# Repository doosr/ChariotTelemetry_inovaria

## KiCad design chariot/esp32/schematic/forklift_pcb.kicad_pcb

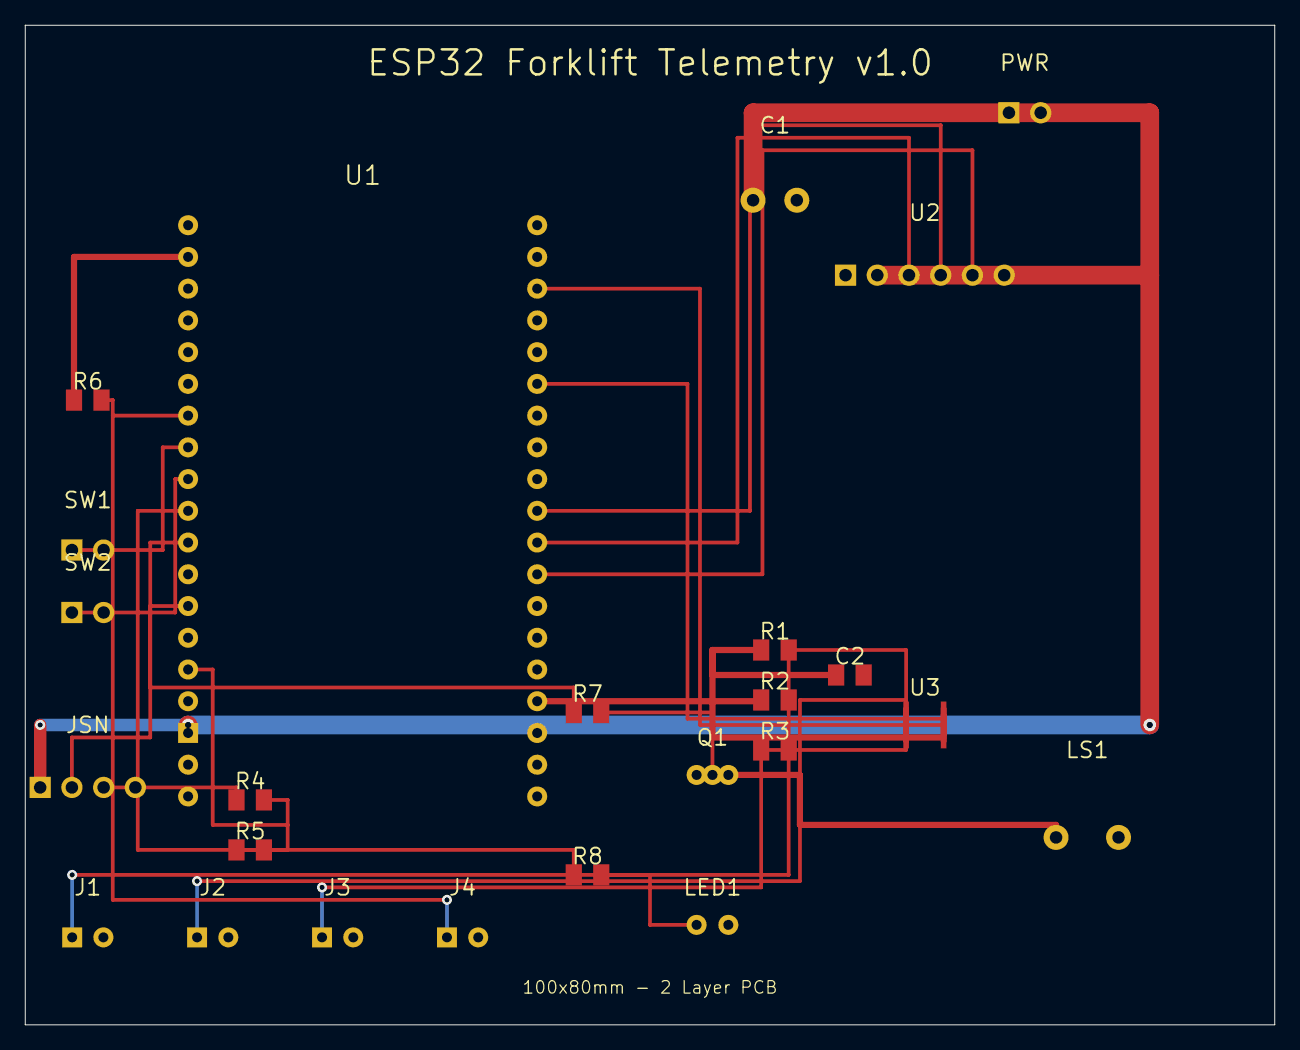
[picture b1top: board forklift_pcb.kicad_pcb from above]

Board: 2 copper layers, 100.0 x 80.0 mm, 24 parts (0 on the bottom side), 20 nets.

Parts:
C1: 100uF 16V; CP_Radial_D8.0mm_P3.50mm
C2: 100nF; C_0805_2012Metric
J1: SENS_OIL; JST_XH_B2B-XH-A_1x02_P2.50mm_Vertical
J2: SENS_FUEL; JST_XH_B2B-XH-A_1x02_P2.50mm_Vertical
J3: SENS_NTC; JST_XH_B2B-XH-A_1x02_P2.50mm_Vertical
J4: SENS_RPM; JST_XH_B2B-XH-A_1x02_P2.50mm_Vertical
JSN: JSN-SR04T; PinHeader_1x04_P2.54mm_Vertical
LED1: LED Green; LED_D3.0mm
LS1: Buzzer 5V; Buzzer_12x9.5mm
PWR: +5V INPUT; PinHeader_1x02_P2.54mm_Vertical
Q1: 2N2222; TO-92_Inline
R1, R2, R3, R5, R7: 1k; R_0805_2012Metric
R4: 2k; R_0805_2012Metric
R6: 10k; R_0805_2012Metric
R8: 330R; R_0805_2012Metric
SW1: FWD Switch; PinHeader_1x02_P2.54mm_Vertical
SW2: REV Switch; PinHeader_1x02_P2.54mm_Vertical
U1: ESP32-DevKitC-32D
U2: SIM808 Module; PinHeader_1x06_P2.54mm_Vertical
U3: ADS1115; MSOP-10_3x3mm_P0.5mm

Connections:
ALARM_5V: LS1.1, Q1.3
ALARM_BUZZER: Q1.2, R7.1, R7.2, U1.L11
FUEL_LEVEL_SIGNAL: J2.1, R2.2, U3.3
GND: C1.2, C2.2, J1.2, J2.2, J3.2, J4.2, JSN.4, LED1.2, LS1.2, PWR.2, Q1.1, R3.2, R5.2, SW1.2, SW2.2, U1.L1, U1.L16, U1.R1, U1.R15, U2.1, U3.1, U3.7
I2C_SCL: U1.R3, U3.8
I2C_SDA: U1.R6, U3.9
JSN_ECHO: R4.2, R5.1, U1.L15
JSN_ECHO_5V: JSN.3, R4.1
JSN_TRIG: JSN.2, U1.L13
NTC_TEMP_SIGNAL: J3.1, R3.1, U3.5
OIL_LED: LED1.1, R8.1, R8.2, U1.L10
OIL_PRESSURE_SIGNAL: J1.1, R1.2, U3.2
RPM_SENSOR: J4.1, R6.2, U1.L7
SIM808_PWR_KEY: U1.R12, U2.5
SIM808_RX: U1.R11, U2.3
SIM808_TX: U1.R10, U2.4
TRANS_FWD: SW1.1, U1.L8
TRANS_REV: SW2.1, U1.L9
VCC_3V3: C2.1, R1.1, R2.1, R6.1, U1.L2, U1.R16, U3.6
VCC_5V: C1.1, JSN.1, PWR.1, U1.L17, U2.2

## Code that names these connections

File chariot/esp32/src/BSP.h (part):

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// NEW: ADS1115 Channel 3 - 16-bit external ADC
// #define NTC_TEMPERATURE_PIN     34      // OLD - Now available as spare GPIO
// ========== I2C BUS CONFIGURATION ==========
#define I2C_SDA_PIN 21       // Default I2C SDA
#define I2C_SCL_PIN 22       // Default I2C SCL
#define I2C_FREQUENCY 100000 // 100 kHz
// ADS1115 I2C Address
#define ADS1115_I2C_ADDRESS 0x48 // Default address (ADDR -> GND)
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#define ADS1115_CH_SPARE_1 2         // Channel 2: Available
#define ADS1115_CH_NTC_TEMPERATURE 3 // Channel 3: NTC Temperature Sensor (NEW!)
// ========== SIM808 MODULE CONFIGURATION ==========
#define SIM808_PWR_KEY_PIN 4  // Power key pin
#define SIM808_UART_RX 16     // ESP32 RX <- SIM808 TX
#define SIM808_UART_TX 17     // ESP32 TX -> SIM808 RX
#define SIM808_UART_NUM 2     // Hardware UART2
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// #define SIM808_RESET_PIN     5
// #define SIM808_STATUS_PIN    18
// ========== RPM SENSOR CONFIGURATION ==========
#define RPM_SENSOR_PIN 35    // GPIO 35 (Input only, REQUIRES EXTERNAL PULLUP)
#define RPM_PULSES_PER_REV 1 // Number of magnets/pulses per revolution
#define RPM_TIMEOUT_MS 1000  // If no pulse for 1s, RPM = 0
// ========== TRANSMISSION SENSORS (Mano AV/AR) ==========
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
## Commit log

2026-04-12 chariot
2026-04-13 chariot1
2026-04-13 chariot2
2026-04-13 chariot3
